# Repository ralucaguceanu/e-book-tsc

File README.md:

## OpenBook-E-Book-Reader - _Guceanu Raluca-Zinca-Ioana - 331CD_

### Diagrama bloc a proiectului

---

### BOM (Bill Of Materials) cu componentele 3D folosite

| Cantitate | Componentă               | Mouser Link | Datasheet Link |
|-----|--------------------------|-------------|----------------|
| 30  | RC0402FR-07100KL        | [link](https://ro.mouser.com/ProductDetail/YAGEO/RC0402FR-07100KL?qs=mnq%2FyloZIXzTlUn7JAHSWg%3D%3D)    | [link](https://ro.mouser.com/datasheet/2/447/YAGEO_PYu_RC_Group_51_RoHS_L_12-3313492.pdf)       |
| 26  | C0402C560J4HACAUTO      | [link](https://ro.mouser.com/ProductDetail/KEMET/C0402C560J4HACAUTO?qs=j%252B1pi9TdxUae00jFMoJVSQ%3D%3D)    | [link](https://ro.mouser.com/datasheet/2/447/KEM_C1007_X8R_ULTRA_150C_SMD-3316375.pdf)       |
| 6   | PGB1010603MR            | [link](https://ro.mouser.com/ProductDetail/Littelfuse/PGB1010603MR?qs=gu7KAQ731URLg4GSnNNN7Q%3D%3D)    | [link](https://www.littelfuse.com/assetdocs/pulseguard-esd-suppressors-pgb1-datasheet?assetguid=8a337998-d54d-466b-be4e-dc5bcd1f9321)       |
| 3   | EVQPU-JA-02K            | [link](https://ro.mouser.com/ProductDetail/Panasonic/EVQ-PUJ02K?qs=Pa1bP%252BeMzadWe338tXJdGA%3D%3D&utm_id=6470900573&utm_source=google&utm_medium=cpc&utm_marketing_tactic=emeacorp&gad_source=1&gclid=Cj0KCQjwhr6_BhD4ARIsAH1YdjDojUOy3z-znw0CDIjpGvdt6bcYKm_o6AbZvCk-vG340hQQp_eIiz0aAl0iEALw_wcB)    | [link](https://4donline.ihs.com/images/VipMasterIC/IC/PANA/PANA-S-A0003211477/PANA-S-A0004028532-1.pdf?hkey=CECEF36DEECDED6468708AAF2E19C0C6)       |
| 3   | MBR0530                 | [link](https://ro.mouser.com/ProductDetail/onsemi/MBR0530T3G?qs=3JMERSakebpEmdUS6GetdQ%3D%3D)    | [link](https://www.onsemi.com/PowerSolutions/product.do?id=MBR0530T3G)       |
| 2   | SD0805S020S1R0          | [link](https://ro.mouser.com/ProductDetail/KYOCERA-AVX/SD0805S020S1R0?qs=jCA%252BPfw4LHbpkAoSnwrdjw%3D%3D)    | [link](https://ro.mouser.com/datasheet/2/40/schottky-3165252.pdf)       |
| 2   | Si1308EDL-T1-GE3        | [link](https://ro.mouser.com/ProductDetail/Vishay-Semiconductors/SI1308EDL-T1-GE3?qs=bX1%252BNvsK%2FBramh9tgpOaEw%3D%3D)    | [link](https://www.vishay.com/doc?63399)       |
| 1   | USBLC6-2SC6Y            | [link](https://ro.mouser.com/ProductDetail/STMicroelectronics/USBLC6-2SC6Y?qs=gNDSiZmRJS%2FOgDexvXkdow%3D%3D)    | [link](https://ro.mouser.com/datasheet/2/389/usblc6_2sc6y-1852505.pdf)       |
| 1   | BD5229G-TR              | [link](https://ro.mouser.com/ProductDetail/ROHM-Semiconductor/BD5229G-TR?qs=4kLU8WoGk0vvnhrrYwdszw%3D%3D)    | [link](https://fscdn.rohm.com/en/products/databook/datasheet/ic/power/voltage_detector/bd52xxg-e.pdf)       |
| 1   | XC6220A331MR-G          | [link](https://ro.mouser.com/ProductDetail/Torex-Semiconductor/XC6220A331MR-G?qs=AsjdqWjXhJ8ZSWznL1J0gg%3D%3D)    | [link](https://ro.mouser.com/datasheet/2/760/xc6220-3371556.pdf)       |
| 1   | FH34SRJ-24S-0.5SH_99_   | [link](https://ro.mouser.com/ProductDetail/Hirose-Connector/FH34SRJ-24S-0.5SH99?qs=vcbW%252B4%252BSTIpKBl5ap9J8Fw%3D%3D)    | [link](https://ro.mouser.com/datasheet/2/185/FH34SRJ_24S_0_5SH_99__CL0580_1255_6_99_2DDrawing_0-1615044.pdf)       |
| 1   | USB4110-GF-A            | [link](https://ro.mouser.com/ProductDetail/GCT/USB4110-GF-A?qs=KUoIvG%2F9IlYiZvIXQjyJeA%3D%3D)    | [link](https://ro.mouser.com/datasheet/2/837/GCT_USB4110_Product_Drawing___20k_cycles-3455479.pdf)       |
| 1   | 112A-TAAR-R03_ATTEND    | [link](https://www.digikey.ro/ro/products/detail/attend-technology/112A-TAAR-R03/17633923)    | [link](https://www.attend.com.tw/data/download/file/112A-TAAR-R03_Spec.pdf)       |
| 1   | TPC-4828                | [link](https://ro.mouser.com/ProductDetail/Wurth-Elektronik/744065151?qs=PGXP4M47uW53TYf%2FkIVaSQ%3D%3D)    | [link](https://www.we-online.com/components/products/datasheet/744065151.pdf)       |
| 1   | LG_R971-KN-1            | [link](https://ro.mouser.com/ProductDetail/ams-OSRAM/LG-R971-KN-1?qs=LsPilcdHE7EX1EB7GCLHxg%3D%3D)    | [link](https://ro.mouser.com/datasheet/2/588/prd_pim_datasheet_2191277_EN_pdf-3419125.pdf)       |
| 1   | MCP73831T-2ATI_OT       | [link](https://ro.mouser.com/ProductDetail/Microchip-Technology/MCP73831T-2ATI-OT?qs=yUQqVecv4qsZbioEUu%252B83g%3D%3D)    | [link](https://ro.mouser.com/datasheet/2/268/MCP73831_Family_Data_Sheet_DS20001984H-3441711.pdf)       |
| 1   | PFMF.050.2              | [link](https://ro.mouser.com/ProductDetail/Schurter/PFMF.050.2?qs=1auRipcfynCums5v1iucSA%3D%3D)    | [link](https://ro.mouser.com/datasheet/2/358/typ_PFMF-1275918.pdf)       |
| 1   | DMG2305UX-7             | [link](https://ro.mouser.com/ProductDetail/Diodes-Incorporated/DMG2305UX-7?qs=L1DZKBg7t5F%2FNBHrjfxC%252Bg%3D%3D)    | [link](https://www.diodes.com/assets/Datasheets/DMG2305UX.pdf)       |
| 1   | BME688                  | [link](https://ro.mouser.com/ProductDetail/Bosch-Sensortec/BME688?qs=IS%252B4QmGtzzqQoVDscqwx3A%3D%3D)    | [link](https://ro.mouser.com/datasheet/2/783/bst_bme688_fl000-2307034.pdf)       |
| 1   | CPH3225A                | [link](https://ro.mouser.com/ProductDetail/Seiko-Semiconductors/CPH3225A?qs=3etwrb1wR%252BhUOph6lAO7eg%3D%3D)    | [link](https://ro.mouser.com/datasheet/2/360/Seiko_Instruments_MicroBattery_E_20230330_2024Jan_-3561061.pdf)       |
| 1   | W25Q512JVEIQ            | [link](https://ro.mouser.com/ProductDetail/Winbond/W25Q512JVEIQ?qs=l7cgNqFNU1jw6svr3at6tA%3D%3D)    | [link](https://ro.mouser.com/datasheet/2/949/Winbond_W25Q512JV_Datasheet-3240039.pdf)       |
| 1   | ESP32-C6-WROOM-1-N8     | [link](https://ro.mouser.com/ProductDetail/Espressif-Systems/ESP32-C6-WROOM-1-N8?qs=8Wlm6%252BaMh8ST02Gmwp74cw%3D%3D)    | [link](https://ro.mouser.com/datasheet/2/891/Espressif_ESP32_C6_WROOM_1__Datasheet_V0_1_PRELIMI-3239987.pdf)       |
| 1   | DS3231SN#               | [link](https://ro.mouser.com/ProductDetail/Analog-Devices-Maxim-Integrated/DS3231SN?qs=1eQvB6Dk1vhUlr8%2FOrV0Fw%3D%3D)    | [link](https://ro.mouser.com/datasheet/2/609/DS3231-3421123.pdf)       |
| 1   | MAX17048G+T10           | [link](https://ro.mouser.com/ProductDetail/Analog-Devices-Maxim-Integrated/MAX17048G%2bT10?qs=D7PJwyCwLAoGnnn8jEPRBQ%3D%3D)    | [link](https://ro.mouser.com/datasheet/2/609/MAX17048_MAX17049-3469099.pdf)       |
| 1   | Ada 4328                | [link](https://ro.mouser.com/ProductDetail/Adafruit/4328?qs=wnTfsH77Xs6Ypm3wH0xoXg%3D%3D)    | [link](https://www.snapeda.com/parts/4328/Adafruit/view-part/?ref=mouser)       |
| 1   | T491B226K006AT          | [link](https://ro.mouser.com/ProductDetail/KEMET/T491B226K006AT?qs=jcsBHvPDQt8yMdJgz62biA%3D%3D)    | [link](https://ro.mouser.com/datasheet/2/447/KEM_T2005_T491-3316937.pdf)       |

---

### Descrierea Funcționalității Hardware a Ebook Reader-ului

Ebook readerul proiectat utilizează o arhitectură bazată pe microcontrolerul ESP32-C6, integrând multiple module pentru a oferi funcționalități avansate de afișare, stocare, conectivitate și monitorizare. Următoarea descriere detaliază componentele utilizate, interfețele de comunicare, specificațiile hardware și calculele de consum energetic.

---

### 1. Microcontroller Principal: ESP32-C6
- **Rol:** Controlul central al ebook readerului, procesare date și comunicație wireless.
- **Specificații:**
  - Interfețe: SPI, I2C, USB.
  - Alimentare: 3.3V.

**Interfațare cu module:**
- **E-Paper Display:** Interfață SPI pentru transfer rapid de date grafice.
- **Memorie NOR Flash:** SPI pentru stocare firmware și resurse grafice.
- **SD Card:** SPI pentru fișiere ebook.
- **RTC DS3231SN:** I2C pentru menținerea orei și alarme.
- **BME688 Sensor:** I2C pentru monitorizare mediu.
- **Baterie Li-Po:** I2C pentru monitorizarea prin Fuel Gauge (MAX17048).
- **USB-C:** Alimentare și transfer de date.
- **Qwiic/Stemma QT:** Conectarea rapidă a modulelor suplimentare.

---

### 2. Alimentare și Management Energie
- **Modul de Alimentare USB-C:** Asigură 5V pentru încărcare și comunicație USB 2.0.
- **LDO Voltage Regulator:** Convertor 5V -> 3.3V pentru alimentarea modulelor.
- **Protecție ESD:** TVS pe liniile USB pentru protecție la supratensiuni.
- **Baterie Li-Po:** Monitorizare prin MCP73831 și MAX17048 pentru încărcare și nivel de baterie.
- **Supercapacitor:** Menținerea energiei pe termen scurt.

**Calcul Consum:**
- Consum total estimat în funcționare: ~300 mA la 3.3V.
- În standby: ~50 mA datorită modului de consum redus al ESP32 și e-paper.

---

### 3. Module de Afișare
#### E-Paper Display
- **Control:** Prin interfața SPI (MOSI, MISO, SCK, CS).
- **Alimentare:** Tensiune 3.3V, controlată prin MOSFET pentru economisire.
- **Reset și Busy:** Monitorizate prin GPIO pentru sincronizare.

---

### 4. Stocare Externă
#### NOR Flash W25Q512JVEIQ (64MB)
- **Interfață:** SPI (CS, SCK, MISO, MOSI)
- **Rol:** Stocare firmware și resurse grafice.

#### SD Card
- **Interfață:** SPI pentru citire și scriere rapidă de date ebook.

---

### 5. Senzori și Monitorizare
#### Senzor BME688 (Temperatură, Umiditate, Presiune, Calitate Aer)
- **Interfață:** I2C.
- **Alimentare:** 3.3V.

#### Modulul RTC
- **Interfață:** I2C.
- **Alimentare Backup:** Supercapacitor pentru menținerea timpului în lipsa alimentării principale.
- **DS3231SN:** Menține timpul și data.

---

### 6. Interfața de Utilizator
- **Buton Reset:** Resetare manuală a microcontrollerului.
- **Buton Boot:** Intrare în modul programare.
- **Buton de Schimbare:** Configurabil pentru funcții speciale.

---

### 7. Testare și Monitorizare
- **Test Pads:** Puncte de test pentru măsurarea semnalelor SPI, UART, I2C și tensiuni critice.
- **Protecție ESD:** Pe toate liniile critice pentru prevenirea descărcărilor electrostatice.

---

### 8. Conectivitate Externă
#### Qwiic / Stemma QT
- **Interfață I2C:** Permite adăugarea rapidă de module senzoriale suplimentare.
- **Conectare Modulară:** Permite prototipare rapidă și flexibilă.

---

### Folosirea pinilor ESP32-C6

| Modul                  | Pini                                            | Interfață | Motiv                                                                     | 
| ---------------------- | --------------------------------------------------------- | --------- | -------------------------------------------------------------------------- |
| Modul RTC (DS3231)     | IO0 - INT\_RTC, IO1 - 32KHz, IO18 - RST, IO21 - SDA, IO22 - SCL | I2C       | Menține timpul chiar și atunci când ESP32 este oprit.                    |
| Card MicroSD           | IO2 - MISO, IO4 - SS\_SD, IO6 - SCK, IO7 - MOSI                | SPI       | Permite stocarea și recuperarea fișierelor ebook.                        |
| Memorie Flash Externă (NOR) | IO2 - MISO, IO6 - SCK, IO7 - MOSI, IO11 - Flash CS                   | SPI       | Oferă stocare suplimentară pentru datele aplicației.                     |
| E-Paper Display        | IO3 - BUSY, IO5 - DC, IO6 - SCK, IO7 - MOSI, IO10 - EPD CS, IO23 - RST | SPI       | Transferă datele de imagine către afișaj și controlează starea acestuia. |
| Senzor de Mediu (BME688) | IO21 - SDA, IO22 - SCL                                     | I2C       | Citește temperatura, umiditatea, presiunea și calitatea aerului.         |
| Monitorizare Baterie   | IO21 - SDA, IO22 - SCL                                     | I2C       | Citește tensiunea bateriei și starea de încărcare.                       |
| Diverse               | IO9 - BOOT, IO15 - CHANGE, EN - RESET, NC - Not Connected                          | GPIO      | Intrare de utilizator pentru interacțiunea cu dispozitivul.              |

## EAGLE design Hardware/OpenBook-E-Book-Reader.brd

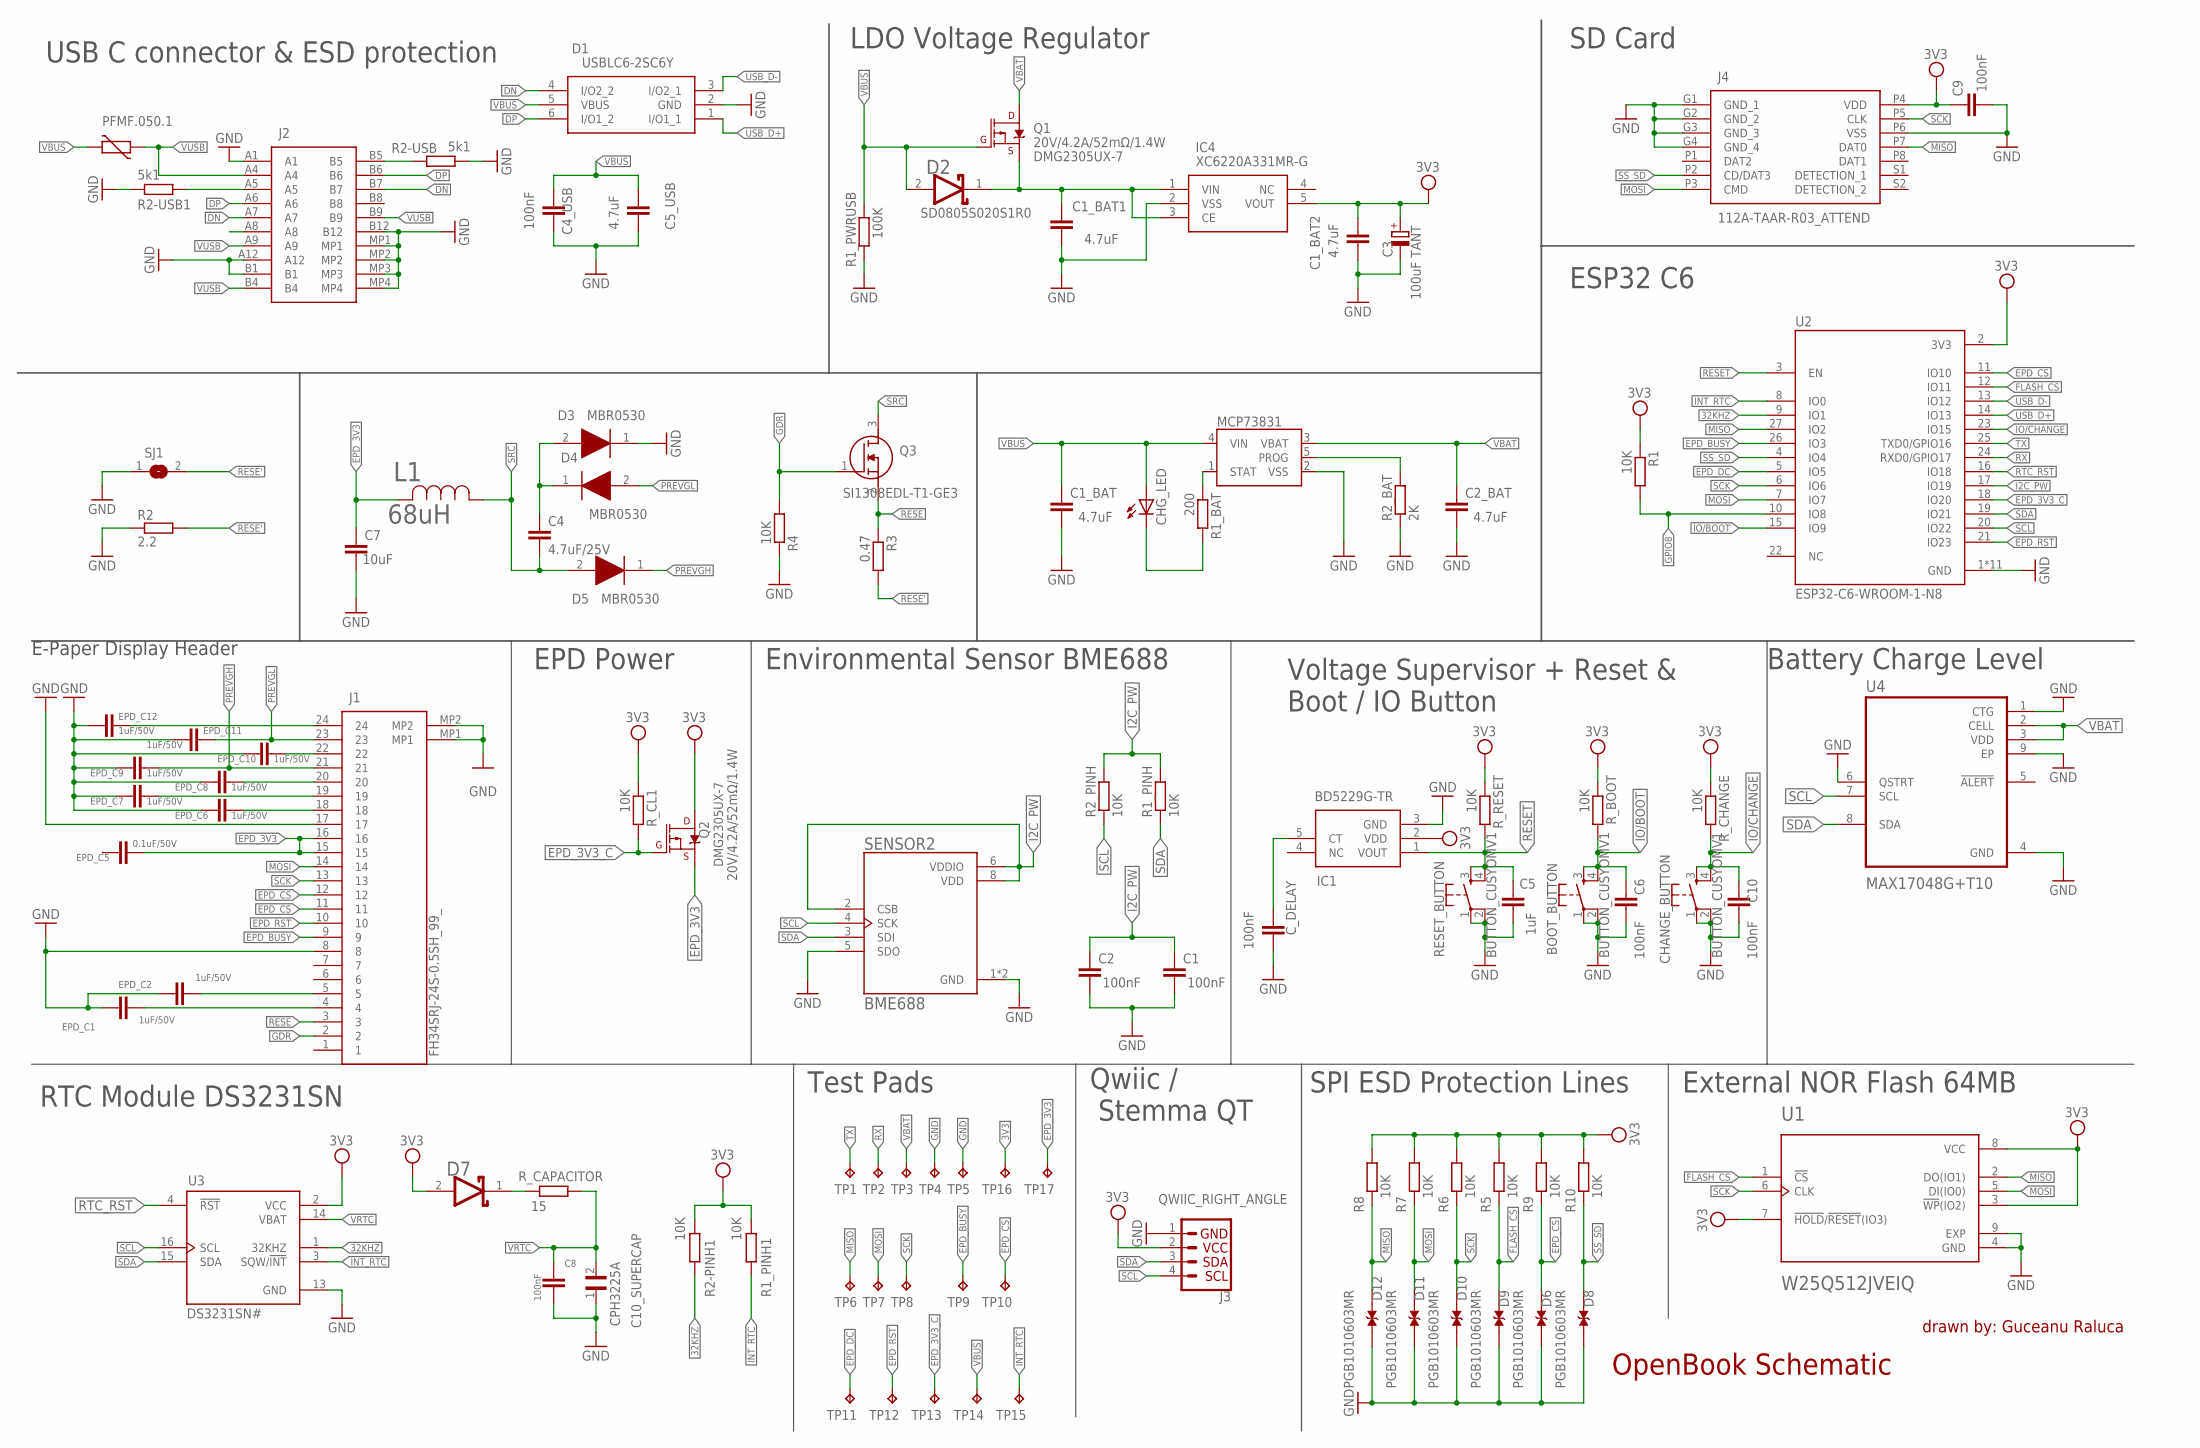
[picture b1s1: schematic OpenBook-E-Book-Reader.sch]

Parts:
BOOT_BUTTON: BUTTON_CUSYOMV1; MYBUTTON
C1, C2, C4_USB, C6, C8, C9, C10: 100nF; ESP32_WROVER_EAGLE-LTSPICE_C0402
C1_BAT, C1_BAT1, C1_BAT2, C2_BAT, C5_USB: 4.7uF; ESP32_WROVER_EAGLE-LTSPICE_C0402
C3: 100uF TANT; RCL_CT3528
C4: 4.7uF/25V; ESP32_WROVER_EAGLE-LTSPICE_C0402
C5: 1uF; ESP32_WROVER_EAGLE-LTSPICE_C0402
C7: 10uF; ESP32_WROVER_EAGLE-LTSPICE_C0402
C10_SUPERCAP: CPH3225A; CAPCP3225X100N
CHANGE_BUTTON: BUTTON_CUSYOMV1; MYBUTTON
CHG_LED: ADAFRUIT_LEDCHIP-LED0603; ADAFRUIT_CHIP-LED0603
C_DELAY: 100nF; ESP32_WROVER_EAGLE-LTSPICE_C0402
D1: USBLC6-2SC6Y; SOT95P280X145-6N
D2, D7: ESP32_WROVER_AVX---SD0805S020S1R0_AVX_SD0805S020S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; ESP32_WROVER_AVX---SD0805S020S1R0_AVX_SD0805S020S1R0_0
D3, D4, D5: MBR0530; SOD3716X135N
D6, D8, D9, D10, D11, D12: PGB1010603MR; DIOC1608X36N
EPD_C1, EPD_C2, EPD_C6, EPD_C7, EPD_C8, EPD_C9, EPD_C10, EPD_C11, EPD_C12: 1uF/50V; ESP32_WROVER_EAGLE-LTSPICE_C0402
EPD_C5: 0.1uF/50V; ESP32_WROVER_EAGLE-LTSPICE_C0402
IC1: BD5229G-TR; SOT95P280X125-5N
IC4: XC6220A331MR-G; SOT95P280X120-5N
J1: FH34SRJ-24S-0.5SH_99_; FH34SRJ24S05SH99
J2: SAMACSYS_PARTS_USB4110-GF-A; SAMACSYS_PARTS_USB4110GFA
J3: QWIIC_RIGHT_ANGLE; JST04_1MM_RA
J4: 112A-TAAR-R03_ATTEND; 112ATAARR03ATTEND
L1: 68uH; IND_4828-WE-TPC_WRE
MCP73831: ESP32_WROVER_SPARKFUN-IC-POWER_MCP73831; ESP32_WROVER_SPARKFUN-IC-POWER_SOT23-5
PFMF.050.1: ESP32C6_VARISTORCN1812; ESP32C6_VARISTOR_CT/CN1812
Q1, Q2: 20V/4.2A/52mΩ/1.4W; ESP32_WROVER_SPARKFUN-DISCRETESEMI_SOT23-3
Q3: SI1308EDL-T1-GE3; SOT65P210X110-3N
R1, R1_PINH, R1_PINH1, R2-PINH1, R2_PINH, R4, R5, R6, R7, R8, R9, R10: 10K; ESP32_WROVER_EAGLE-LTSPICE_R0402
R1_BAT: 200; ESP32_WROVER_EAGLE-LTSPICE_R0402
R1_PWRUSB: 100K; ESP32_WROVER_EAGLE-LTSPICE_R0402
R2: 2.2; ESP32_WROVER_EAGLE-LTSPICE_R0402
R2-USB, R2-USB1: 5k1; ESP32_WROVER_EAGLE-LTSPICE_R0402
R2_BAT: 2K; ESP32_WROVER_EAGLE-LTSPICE_R0402
R3: 0.47; ESP32_WROVER_EAGLE-LTSPICE_R0402
RESET_BUTTON: BUTTON_CUSYOMV1; MYBUTTON
R_BOOT: 10K; ESP32_WROVER_EAGLE-LTSPICE_R0402
R_CAPACITOR: 15; ESP32_WROVER_EAGLE-LTSPICE_R0402
R_CHANGE: 10K; ESP32_WROVER_EAGLE-LTSPICE_R0402
R_CL1: 10K; ESP32_WROVER_EAGLE-LTSPICE_R0402
R_RESET: 10K; ESP32_WROVER_EAGLE-LTSPICE_R0402
SENSOR2: BME688; ESP32_WROVER_BME680_PSON80P300X300X100-8N
SJ1: SJ
TP1, TP2, TP3, TP4, TP5, TP6, TP7, TP8, TP9, TP10, TP11, TP12, TP13, TP14, TP15, TP16, TP17: TPTP20R; TP20R
U1: W25Q512JVEIQ; SON127P600X800X80-9N
U2: ESP32-C6-WROOM-1-N8; XCVR_ESP32-C6-WROOM-1-N8
U3: DS3231SN#; SOIC127P1032X265-16N
U4: MAX17048G+T10; SON50P200X200X80-9N

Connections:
3V3: C1_BAT2.1, C3.+, C9.1, D7.2 (ANODE), IC1.2 (VDD), IC4.5 (VOUT), J3.2, J4.P4 (VDD), Q2.3 (D), R1.1, R1_PINH1.2, R2-PINH1.2, R5.1, R6.2, R7.2, R8.2, R9.2, R10.2, R_BOOT.1, R_CHANGE.1, R_CL1.1, R_RESET.1, TP16.TP, U1.3 (!WP!(IO2)), U1.7 (!HOLD!/!RESET!(IO3)), U1.8 (VCC), U2.2 (3V3), U3.2 (VCC)
32KHZ: R2-PINH1.1, U2.9 (IO1), U3.1 (32KHZ)
DN: D1.4 (I/O2_2), J2.A7, J2.B7
DP: D1.6 (I/O1_2), J2.A6, J2.B6
EPD_3V3: C7.1, EPD_C5.1, J1.15, J1.16, L1.2, Q2.2 (S), TP17.TP
EPD_3V3_C: Q2.1 (G), R_CL1.2, TP13.TP, U2.18 (IO20)
EPD_BUSY: J1.9, TP9.TP, U2.26 (IO3)
EPD_CS: D6.1, J1.11, J1.12, R9.1, TP10.TP, U2.11 (IO10)
EPD_DC: TP11.TP, U2.5 (IO5)
EPD_RST: J1.10, TP12.TP, U2.21 (IO23)
FLASH_CS: D9.1, R5.2, U1.1 (!CS), U2.12 (IO11)
GDR: J1.2, Q3.1 (G), R4.1
GND: BOOT_BUTTON.1, BOOT_BUTTON.2, C1.2, C1_BAT.2, C1_BAT1.2, C1_BAT2.2, C2.2, C2_BAT.2, C3.-, C4_USB.2, C5.2, C5_USB.2, C6.2, C7.2, C8.2, C9.2, C10.2, C10_SUPERCAP.1, CHANGE_BUTTON.1, CHANGE_BUTTON.2, C_DELAY.2, D1.2 (GND), D3.1 (K), D6.2, D8.2, D9.2, D10.2, D11.2, D12.2, EPD_C1.2, EPD_C2.2, EPD_C6.2, EPD_C7.2, EPD_C8.2, EPD_C9.2, EPD_C10.2, EPD_C11.2, EPD_C12.2, IC1.3 (GND), IC4.2 (VSS), J1.8, J1.17, J1.MP1, J1.MP2, J2.A1, J2.A12, J2.B1, J2.B12, J2.MP1, J2.MP2, J2.MP3, J2.MP4, J3.1, J4.G1 (GND_1), J4.G2 (GND_2), J4.G3 (GND_3), J4.G4 (GND_4), J4.P6 (VSS), MCP73831.2 (VSS), R1_PWRUSB.1, R2.1, R2-USB.2, R2-USB1.1, R2_BAT.1, R4.2, RESET_BUTTON.1, RESET_BUTTON.2, SENSOR2.1 (GND), SENSOR2.5 (SDO), SENSOR2.7 (GND), SJ1.1, TP4.TP, TP5.TP, U1.4 (GND), U1.9 (EXP), U2.1 (GND), U2.28 (GND), U2.29_1 (GND), U2.29_2 (GND), U2.29_3 (GND), U2.29_4 (GND), U2.29_5 (GND), U2.29_6 (GND), U2.29_7 (GND), U2.29_8 (GND), U2.29_9 (GND), U3.13 (GND), U4.1 (CTG), U4.4 (GND), U4.6 (QSTRT), U4.9 (EP)
GPIO8: R1.2, U2.10 (IO8)
I2C_PW: C1.1, C2.1, R1_PINH.2, R2_PINH.2, SENSOR2.2 (CSB), SENSOR2.6 (VDDIO), SENSOR2.8 (VDD), U2.17 (IO19)
INT_RTC: R1_PINH1.1, TP15.TP, U2.8 (IO0), U3.3 (SQW/!INT)
IO/BOOT: BOOT_BUTTON.3, BOOT_BUTTON.4, C6.1, R_BOOT.2, U2.15 (IO9)
IO/CHANGE: C10.1, CHANGE_BUTTON.3, CHANGE_BUTTON.4, R_CHANGE.2, U2.23 (IO15)
MISO: D12.1, J4.P7 (DAT0), R8.1, TP6.TP, U1.2 (DO(IO1)), U2.27 (IO2)
MOSI: D11.1, J1.14, J4.P3 (CMD), R7.1, TP7.TP, U1.5 (DI(IO0)), U2.7 (IO7)
unnamed: J2.B5, R2-USB.1
unnamed: C1_BAT1.1, D2.1 (CATHODE), IC4.1 (VIN), IC4.3 (CE), Q1.2 (S)
unnamed: C4.1, D3.2 (A), D4.1 (K)
unnamed: J2.A5, R2-USB1.2
unnamed: D7.1 (CATHODE), R_CAPACITOR.2
unnamed: CHG_LED.C, R1_BAT.2
unnamed: MCP73831.5 (PROG), R2_BAT.2
unnamed: MCP73831.1 (STAT), R1_BAT.1
unnamed: EPD_C12.1, J1.24
unnamed: C_DELAY.1, IC1.5 (CT)
unnamed: EPD_C10.1, J1.22
unnamed: EPD_C8.1, J1.20
unnamed: EPD_C7.1, J1.19
unnamed: EPD_C6.1, J1.18
unnamed: EPD_C2.1, J1.5
unnamed: EPD_C1.1, J1.4
PREVGH: D5.1 (K), EPD_C9.1, J1.21
PREVGL: D4.2 (A), EPD_C11.1, J1.23
RESE: J1.3, Q3.2 (S), R3.1
RESE': R2.2, R3.2, SJ1.2
RESET: C5.1, IC1.1 (VOUT), RESET_BUTTON.3, RESET_BUTTON.4, R_RESET.2, U2.3 (EN)
RTC_RST: U2.16 (IO18), U3.4 (!RST)
RX: TP2.TP, U2.24 (RXD0/GPIO17)
SCK: D10.1, J1.13, J4.P5 (CLK), R6.1, TP8.TP, U1.6 (CLK), U2.6 (IO6)
SCL: J3.4, R2_PINH.1, SENSOR2.4 (SCK), U2.20 (IO22), U3.16 (SCL), U4.7 (SCL)
SDA: J3.3, R1_PINH.1, SENSOR2.3 (SDI), U2.19 (IO21), U3.15 (SDA), U4.8 (SDA)
SRC: C4.2, D5.2 (A), L1.1, Q3.3 (D)
SS_SD: D8.1, J4.P2 (CD/DAT3), R10.1, U2.4 (IO4)
TX: TP1.TP, U2.25 (TXD0/GPIO16)
USB_D+: D1.1 (I/O1_1), U2.14 (IO13)
USB_D-: D1.3 (I/O2_1), U2.13 (IO12)
VBAT: C2_BAT.1, MCP73831.3 (VBAT), Q1.3 (D), TP3.TP, U4.2 (CELL), U4.3 (VDD)
VBUS: C1_BAT.1, C4_USB.1, C5_USB.1, CHG_LED.A, D1.5 (VBUS), D2.2 (ANODE), MCP73831.4 (VIN), PFMF.050.1.2, Q1.1 (G), R1_PWRUSB.2, TP14.TP
VRTC: C8.1, C10_SUPERCAP.2, R_CAPACITOR.1, U3.14 (VBAT)
VUSB: J2.A4, J2.A9, J2.B4, J2.B9, PFMF.050.1.1

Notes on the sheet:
USB C connector & ESD protection
LDO Voltage Regulator
SD Card
ESP32 C6
E-Paper Display Header
RTC Module DS3231SN
Test Pads
Qwiic / Stemma QT
SPI ESD Protection Lines
External NOR Flash 64MB
Battery Charge Level
Voltage Supervisor + Reset & Boot / IO Button
Environmental Sensor BME688
EPD Power
OpenBook Schematic
drawn by: Guceanu Raluca

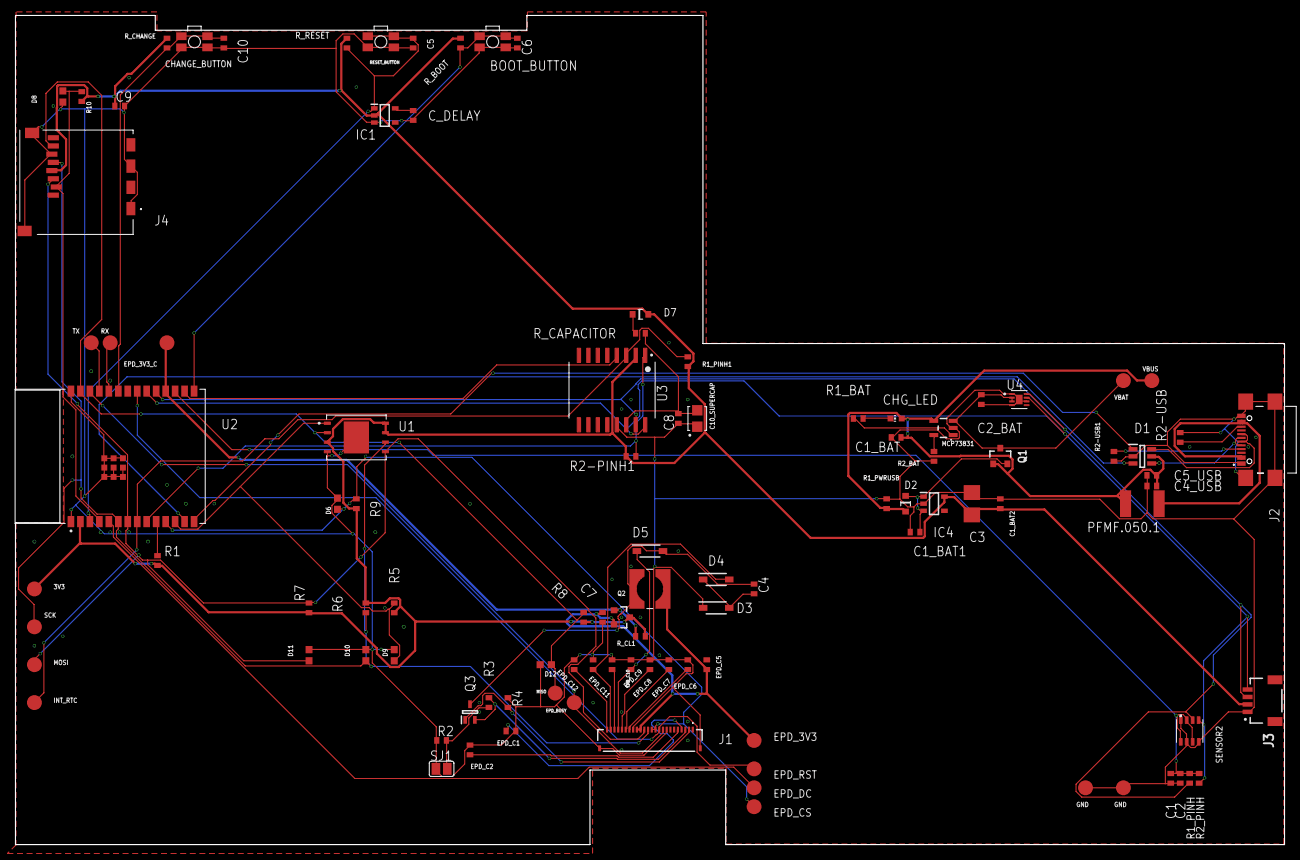
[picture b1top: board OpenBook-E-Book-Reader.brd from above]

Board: 2 copper layers, 170.2 x 111.2 mm, 103 parts (0 on the bottom side), 55 nets.

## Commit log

2025-04-05 add LICENSE
2025-04-05 add hardware and manufacturing files
2025-04-05 add images
2025-04-05 add mechanical file (only .f3z)
2025-04-05 add mechanical file (.step)
2025-04-06 upload Bill-of-Materials.csv
2025-04-06 upload Pick-and-Place.csv
2025-04-06 upload Bill-of-Materials.bom and Pick-and-Place.cpl files
2025-04-16 update OpenBook-E-Book-Reader.brd
    refacerea planului de masa
2025-04-16 update OpenBook-E-Book-Reader.f3z
    rezolvare grosime 3D PCB
2025-04-16 update OpenBook-E-Book-Reader.step for exploded view

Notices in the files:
parts and their libraries:
COPYRIGHT: Copyright (C) 2024 Ultra Librarian. All rights reserved.
